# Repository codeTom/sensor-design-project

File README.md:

#### Arduino shield with an optical pulse sensor and amplifier for LM35 temperature sensor

Designed by

Filip Ayazi, Stephen De Bank, Hayley Gilbert

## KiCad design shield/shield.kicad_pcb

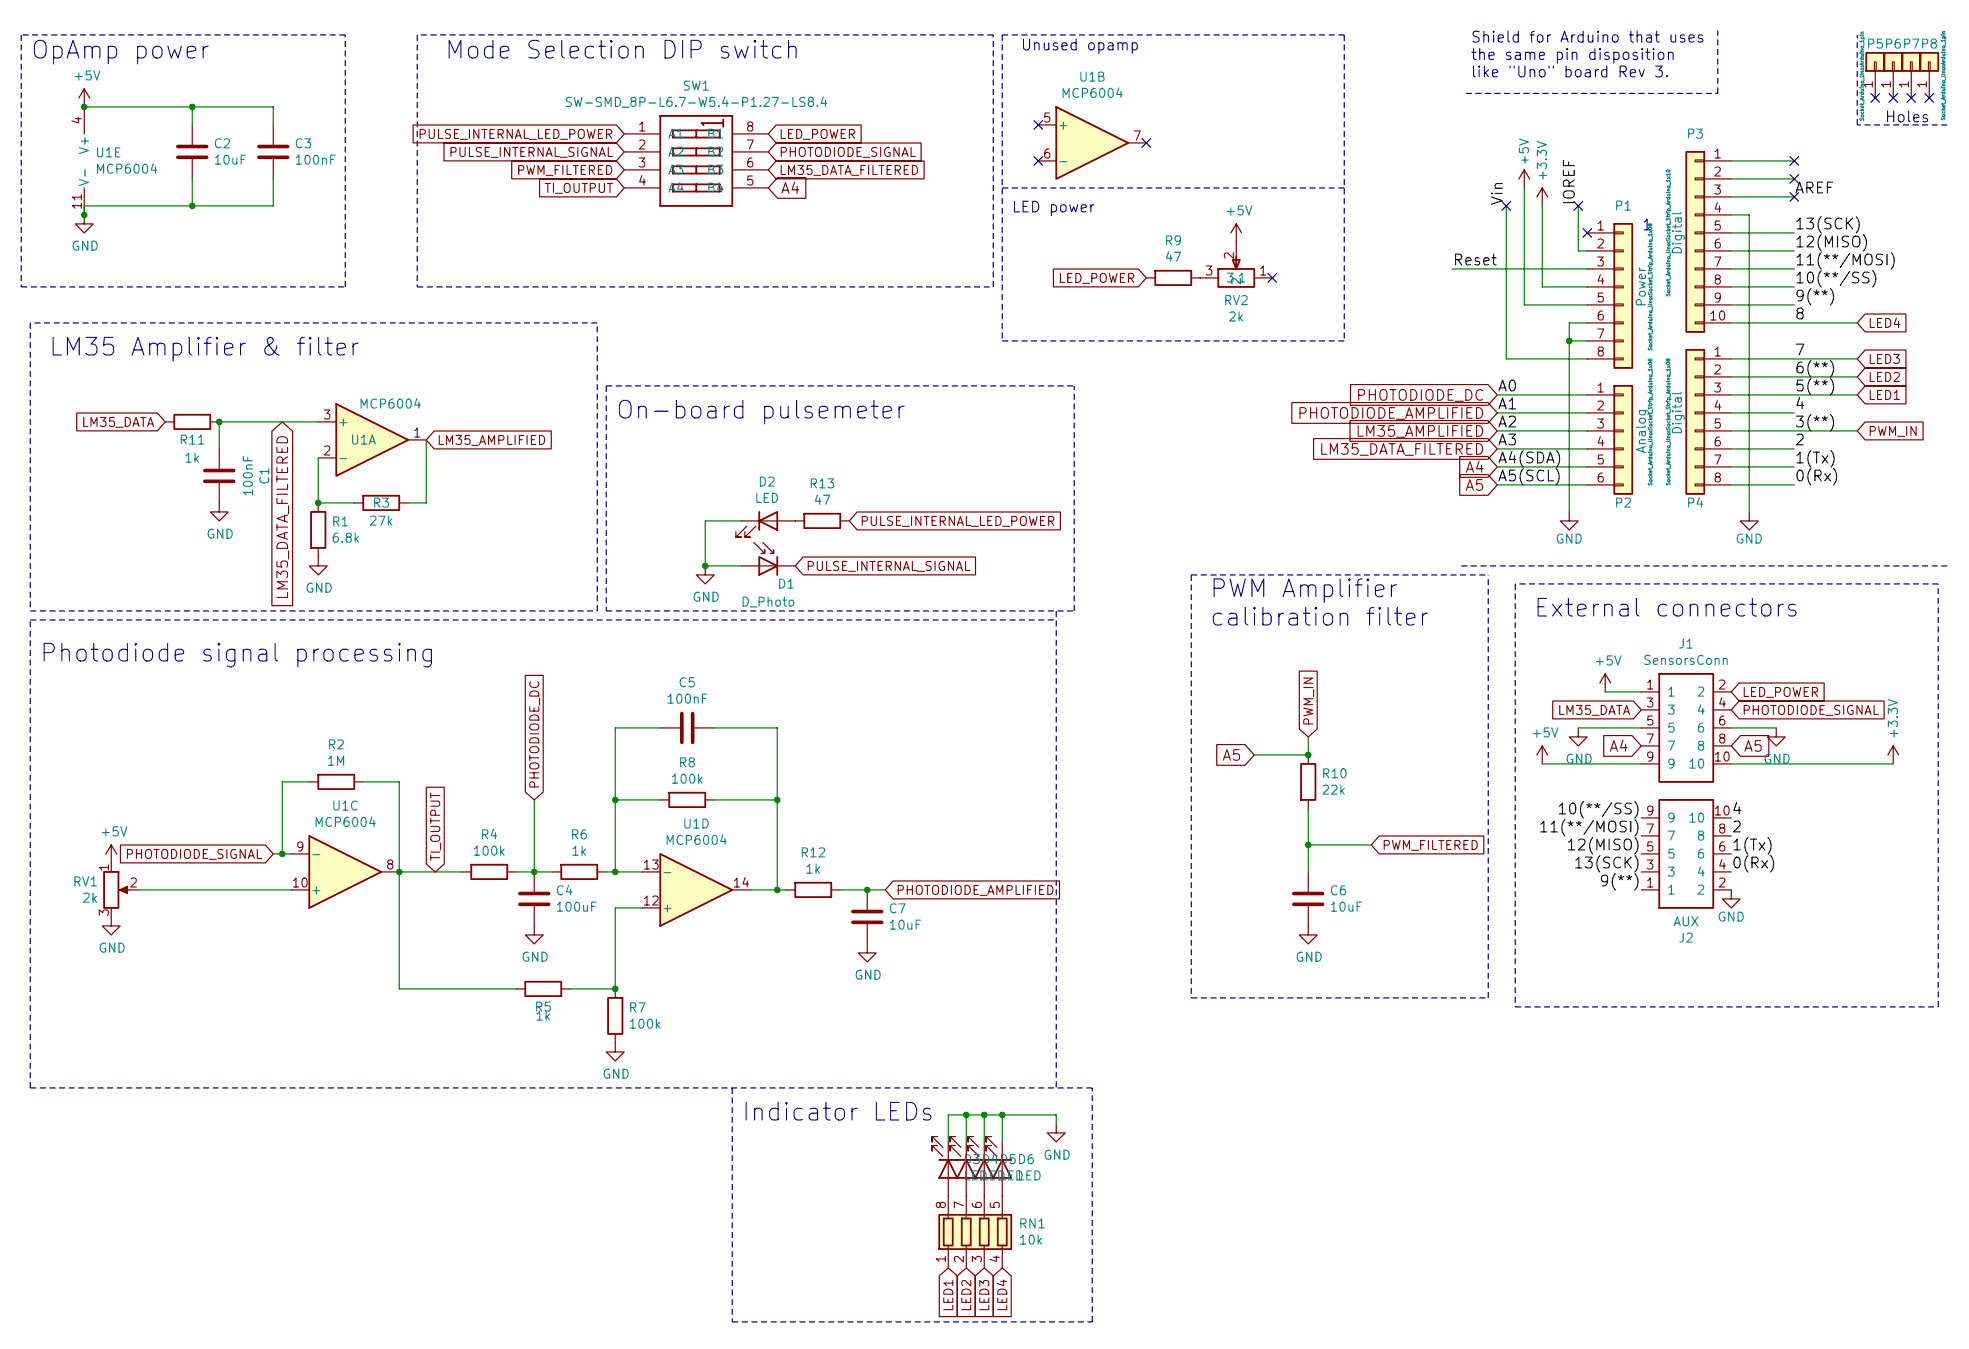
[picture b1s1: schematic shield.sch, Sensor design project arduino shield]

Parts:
C1, C3, C5: 100nF; C_0402_1005Metric; LCSC C1525
C2, C6, C7: 10uF; C_0402_1005Metric; LCSC C15525
C4: 100uF; C_1206_3216Metric; LCSC C15008
D1: D_Photo; LED_1206_3216Metric; LCSC C16746
D2, D3: LED; LED_0805_2012Metric; LCSC C84256
D4: LED; LED_0805_2012Metric; LCSC C2297
D5: LED; LED_0603_1608Metric; LCSC C72041
D6: LED; LED_0805_2012Metric; LCSC C2296
J1: SensorsConn; CONN-SMD_C843271; LCSC C843271
J2: AUX; CONN-SMD_C843271; LCSC C843271
P1: Power; Socket_Strip_Arduino_1x08
P2: Analog; Socket_Strip_Arduino_1x06
P3: Digital; Socket_Strip_Arduino_1x10
P4: Digital; Socket_Strip_Arduino_1x08
P5, P6, P7, P8: CONN_01X01; Arduino_1pin
R1: 6.8k; R_0603_1608Metric; LCSC C23212
R2: 1M; R_0603_1608Metric; LCSC C22935
R3: 27k; R_0603_1608Metric; LCSC C22967
R4, R7, R8: 100k; R_0603_1608Metric; LCSC C25803
R5, R6, R11, R12: 1k; R_0603_1608Metric; LCSC C21190
R9, R13: 47; R_0805_2012Metric; LCSC C17714
R10: 22k; R_0603_1608Metric; LCSC C31850
RN1: 10k; R_Array_Convex_4x0603; LCSC C29718
RV1, RV2: 2k; RES-ADJ-SMD_G43AT; LCSC C128157
SW1: SW-SMD_8P-L6.7-W5.4-P1.27-LS8.4; LCSC C40736
U1: MCP6004; TSSOP-14_4.4x5mm_P0.65mm; LCSC C50282

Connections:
+3V3: J1.10, P1.4
+5V: C2.1, C3.1, J1.1, J1.9, P1.5, RV1.1, RV2.2, U1.4 (V+)
/0(Rx): J2.4, P4.8
/1(Tx): J2.6, P4.7
/2: J2.8, P4.6
/4: J2.10, P4.4
/9(**): J2.1, P3.9
/10(**/SS): J2.9, P3.8
/11(**/MOSI): J2.7, P3.7
/12(MISO): J2.5, P3.6
/13(SCK): J2.3, P3.5
/AREF: P3.3
/IOREF: P1.2
/Reset: P1.3
/Vin: P1.8
A4: J1.7, P2.5, SW1.5 (B4)
A5: J1.8, P2.6, P4.5, R10.1
GND: C1.1, C2.2, C3.2, C4.2, C6.2, C7.2, D1.2 (A), D2.1 (K), D3.1 (K), D4.1 (K), D5.1 (K), D6.1 (K), J1.5, J1.6, J2.2, P1.6, P1.7, P3.4, R1.2, R7.1, RV1.3, U1.11 (V-)
LED1: P4.3, RN1.1 (R1.1)
LED2: P4.2, RN1.2 (R2.1)
LED3: P4.1, RN1.3 (R3.1)
LED4: P3.10, RN1.4 (R4.1)
LED_POWER: J1.2, R9.2, SW1.8 (B1)
LM35_AMPLIFIED: P2.3, R3.1, U1.1
LM35_DATA: J1.3, R11.1
LM35_DATA_FILTERED: C1.2, P2.4, R11.2, SW1.6 (B3), U1.3 (+)
unnamed: C5.1, R8.1, R12.2, U1.14
unnamed: C5.2, R6.1, R8.2, U1.13 (-)
unnamed: D2.2 (A), R13.2
unnamed: D3.2 (A), RN1.8 (R1.2)
unnamed: D4.2 (A), RN1.7 (R2.2)
unnamed: D5.2 (A), RN1.6 (R3.2)
unnamed: D6.2 (A), RN1.5 (R4.2)
unnamed: R1.1, R3.2, U1.2 (-)
unnamed: R5.2, R7.2, U1.12 (+)
unnamed: R9.1, RV2.3
unnamed: RV1.2, U1.10 (+)
PHOTODIODE_AMPLIFIED: C7.1, P2.2, R12.1
PHOTODIODE_DC: C4.1, P2.1, R4.1, R6.2
PHOTODIODE_SIGNAL: J1.4, R2.2, SW1.7 (B2), U1.9 (-)
PULSE_INTERNAL_LED_POWER: R13.1, SW1.1 (A1)
PULSE_INTERNAL_SIGNAL: D1.1 (K), SW1.2 (A2)
PWM_FILTERED: C6.1, R10.2, SW1.3 (A3)
TI_OUTPUT: R2.1, R4.2, R5.1, SW1.4 (A4), U1.8

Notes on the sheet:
Holes
Shield for Arduino that uses the same pin disposition like "Uno" board Rev 3.
External connectors
PWM Amplifier calibration filter
LM35 Amplifier & filter
OpAmp power
Mode Selection DIP switch
On-board pulsemeter
Unused opamp
Photodiode signal processing
LED power
Indicator LEDs

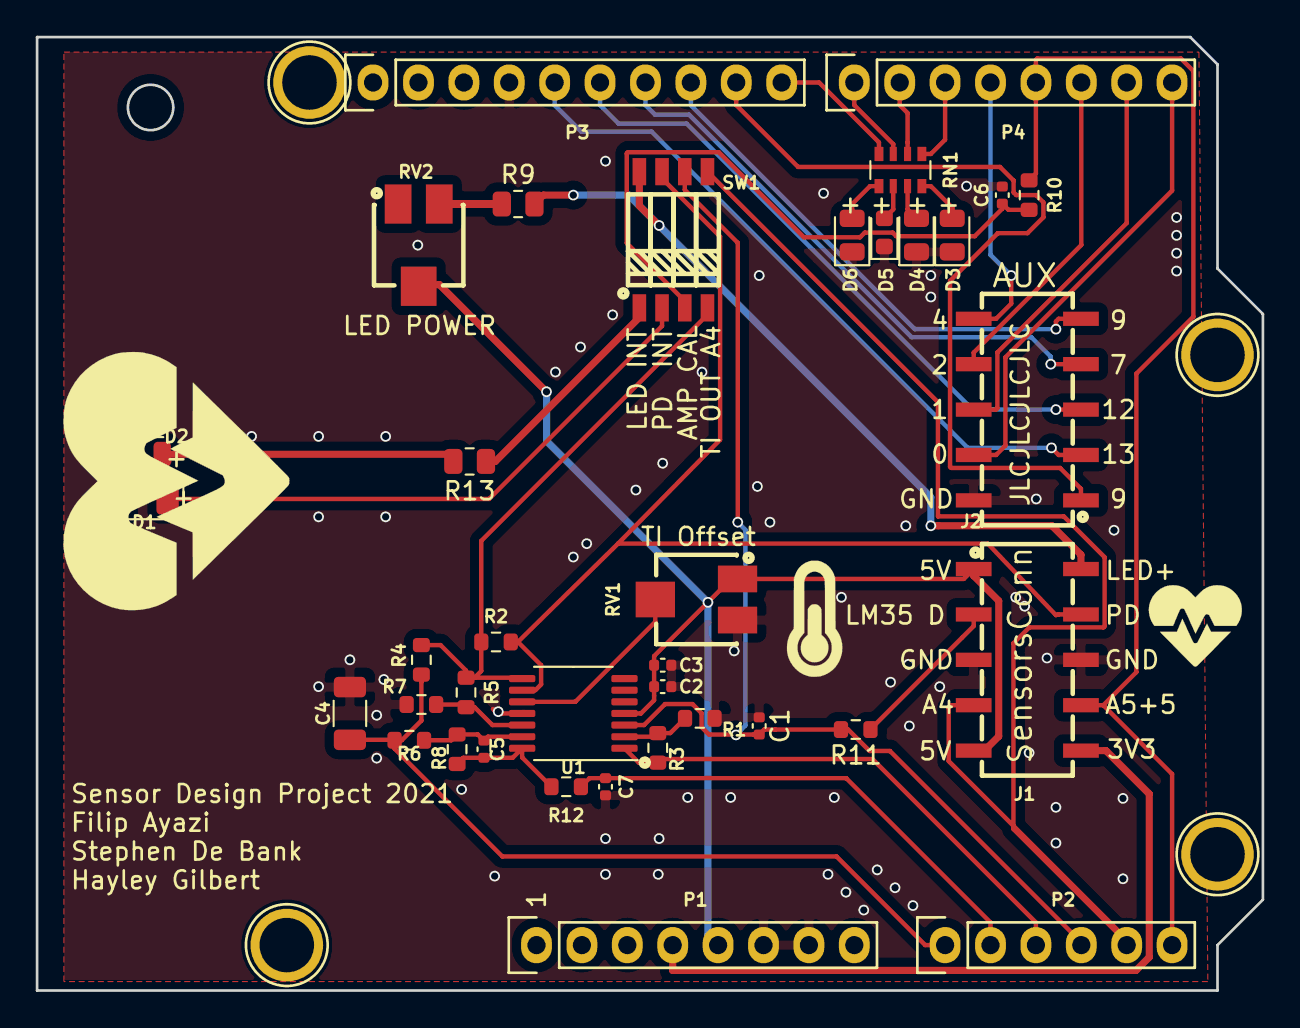
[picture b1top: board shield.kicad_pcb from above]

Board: 2 copper layers, 68.6 x 53.3 mm, 41 parts (0 on the bottom side), 40 nets.

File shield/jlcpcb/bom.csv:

Comment,Designator,Footprint,LCSC
Power,P1,Socket_Arduino_Uno:Socket_Strip_Arduino_1x08,
Analog,P2,Socket_Arduino_Uno:Socket_Strip_Arduino_1x06,
CONN_01X01,"P5,P6,P7,P8",Socket_Arduino_Uno:Arduino_1pin,
Digital,P4,Socket_Arduino_Uno:Socket_Strip_Arduino_1x08,
Digital,P3,Socket_Arduino_Uno:Socket_Strip_Arduino_1x10,
MCP6004,U1,Package_SO:TSSOP-14_4.4x5mm_P0.65mm,C50282
27k,R3,Resistor_SMD:R_0603_1608Metric,C22967
6.8k,R1,Resistor_SMD:R_0603_1608Metric,C23212
D_Photo,D1,LED_SMD:LED_1206_3216Metric,C16746
LED,"D2,D3",LED_SMD:LED_0805_2012Metric,C84256
47,"R9,R13",Resistor_SMD:R_0805_2012Metric,C17714
22k,R10,Resistor_SMD:R_0603_1608Metric,C31850
10uF,"C6,C7,C2",Capacitor_SMD:C_0402_1005Metric,C15525
1M,R2,Resistor_SMD:R_0603_1608Metric,C22935
100k,"R4,R8,R7",Resistor_SMD:R_0603_1608Metric,C22936
100uF,C4,Capacitor_SMD:C_1206_3216Metric,C15008
1k,"R6,R5,R12,R11",Resistor_SMD:R_0603_1608Metric,C21190
100nF,"C5,C3,C1",Capacitor_SMD:C_0402_1005Metric,C1525
2k,"RV1,RV2",lcscimport:RES-ADJ-SMD_G43AT,C128157
10k,RN1,Resistor_SMD:R_Array_Convex_4x0603,C29718
LED,D4,LED_SMD:LED_0805_2012Metric,C2297
LED,D5,LED_SMD:LED_0603_1608Metric,C72041
LED,D6,LED_SMD:LED_0805_2012Metric,C2296
SensorsConn,J1,lcscimport:CONN-SMD_C843271,C843271
AUX,J2,lcscimport:CONN-SMD_C843271,C843271
SW-SMD_8P-L6.7-W5.4-P1.27-LS8.4,SW1,lcscimport:SW-SMD_8P-L6.7-W5.4-P1.27-LS8.4,C40736

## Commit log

2021-12-16 Create Octave
2021-12-16 Add 3D printed finger holder
